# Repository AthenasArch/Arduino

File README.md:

# Arduino - ESP8266 - ESP32 - STM32
- Projetos programados utilizando a interface do Arduino.

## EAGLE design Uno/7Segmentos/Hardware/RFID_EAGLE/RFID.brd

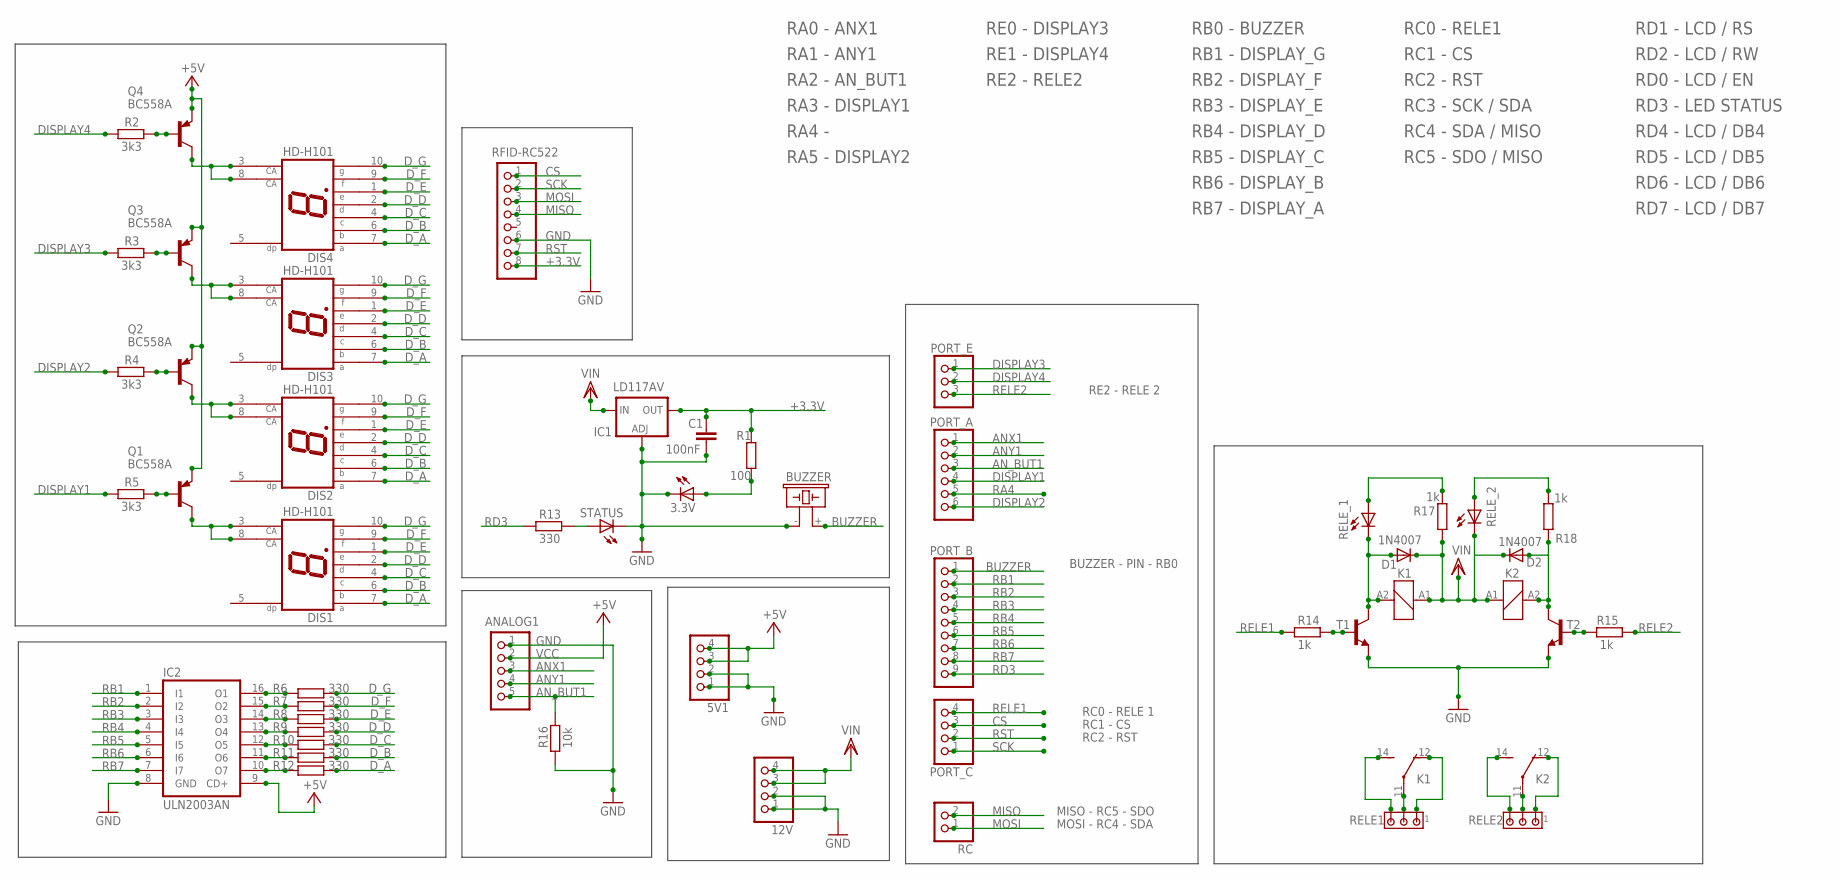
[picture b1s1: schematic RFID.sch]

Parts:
3.3V: LED5MM
5V: BUZZER; F/CM12P
5V1, 12V: PINHD-1X4; 1X04
ANALOG1: PINHD-1X5; 1X05
C1: 100nF; C050-025X075
D1, D2: 1N4007; DO41-10
DIS1, DIS2, DIS3, DIS4: HD-H101; HDSP-M
IC1: LD117AV; TO220L1
IC2: ULN2003AN; DIL16
JP1: RFID-RC522; 1X08
K1, K2: ZNS5106; ZN5
PORT_A: PINHD-1X6; 1X06
PORT_B: PINHD-1X9; 1X09
PORT_C: PINHD-1X4; 1X04
PORT_E: PINHD-1X3; 1X03
Q1, Q2, Q3, Q4: BC558A; TO92-EBC
R1: 100; 0207/10
R2, R3, R4, R5: 3k3; 0207/10
R6, R7, R8, R9, R10, R11, R12, R13: 330; 0207/10
R14, R15, R17, R18: 1k; 0207/10
R16: 10k; 0207/10
RC: PINHD-1X2; 1X02
RELE1, RELE2: MTA03-156; 1X3MTA
RELE_1, RELE_2: LED5MM
STATUS: LED5MM
T1, T2: BC548-NPN-TO92-CBE; TO92-CBE

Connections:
+3.3V: C1.1, IC1.2 (OUT), JP1.8, R1.2
ANX1: ANALOG1.3, PORT_A.1
ANY1: ANALOG1.4, PORT_A.2
AN_BUT1: ANALOG1.5, PORT_A.3, R16.1
BUZZER: 5V.+ (1), PORT_B.1
CS: JP1.1, PORT_C.3
DISPLAY1: PORT_A.4, R5.2
DISPLAY2: PORT_A.6, R4.2
DISPLAY3: PORT_E.1, R3.2
DISPLAY4: PORT_E.2, R2.2
D_A: DIS1.7 (A), DIS2.7 (A), DIS3.7 (A), DIS4.7 (A), R12.1
D_B: DIS1.6 (B), DIS2.6 (B), DIS3.6 (B), DIS4.6 (B), R11.1
D_C: DIS1.4 (C), DIS2.4 (C), DIS3.4 (C), DIS4.4 (C), R10.1
D_D: DIS1.2 (D), DIS2.2 (D), DIS3.2 (D), DIS4.2 (D), R9.1
D_E: DIS1.1 (E), DIS2.1 (E), DIS3.1 (E), DIS4.1 (E), R8.1
D_F: DIS1.9 (F), DIS2.9 (F), DIS3.9 (F), DIS4.9 (F), R7.1
D_G: DIS1.10 (G), DIS2.10 (G), DIS3.10 (G), DIS4.10 (G), R6.1
GND: 3.3V.K (C), 5V.- (2), 5V1.1, 5V1.2, 12V.1, 12V.2, ANALOG1.1, C1.2, IC1.1 (ADJ), IC2.8 (GND), JP1.6, R16.2, STATUS.K (C), T1.E, T2.E
MISO: JP1.4, RC.2
MOSI: JP1.3, RC.1
unnamed: 3.3V.A, R1.1
unnamed: DIS4.3 (CA), DIS4.8 (CA), Q4.C
unnamed: Q1.B, R5.1
unnamed: Q2.B, R4.1
unnamed: Q3.B, R3.1
unnamed: Q4.B, R2.1
unnamed: IC2.16 (O1), R6.2
unnamed: IC2.15 (O2), R7.2
unnamed: IC2.14 (O3), R8.2
unnamed: IC2.13 (O4), R9.2
unnamed: IC2.12 (O5), R10.2
unnamed: IC2.11 (O6), R11.2
unnamed: IC2.10 (O7), R12.2
unnamed: D2.A, K2.A2 (2), R18.2, T2.C
unnamed: R13.1, STATUS.A
unnamed: D1.A, K1.A2 (2), RELE_1.K (C), T1.C
unnamed: R14.1, T1.B
unnamed: K1.11, RELE1.2
unnamed: R15.2, T2.B
unnamed: K1.12 (O), RELE1.1
unnamed: K1.14 (S), RELE1.3
unnamed: K2.11, RELE2.2
unnamed: K2.14 (S), RELE2.3
unnamed: K2.12 (O), RELE2.1
unnamed: R17.2, RELE_1.A
unnamed: R18.1, RELE_2.A
RA4: PORT_A.5
RB1: IC2.1 (I1), PORT_B.2
RB2: IC2.2 (I2), PORT_B.3
RB3: IC2.3 (I3), PORT_B.4
RB4: IC2.4 (I4), PORT_B.5
RB5: IC2.5 (I5), PORT_B.6
RB6: IC2.6 (I6), PORT_B.7
RB7: IC2.7 (I7), PORT_B.8
RD3: PORT_B.9, R13.2
RELE1: PORT_C.4, R14.2
RELE2: PORT_E.3, R15.1
RST: JP1.7, PORT_C.2
SCK: JP1.2, PORT_C.1
VCC: 5V1.3, 5V1.4, ANALOG1.2, IC2.9 (CD+), Q1.E, Q2.E, Q3.E, Q4.E
VCC1: DIS3.3 (CA), DIS3.8 (CA), Q3.C
VCC2: DIS2.3 (CA), DIS2.8 (CA), Q2.C
VCC3: DIS1.3 (CA), DIS1.8 (CA), Q1.C
VDD: 12V.3, 12V.4, D1.C, D2.C, IC1.3 (IN), K1.A1 (1), K2.A1 (1), R17.1, RELE_2.K (C)

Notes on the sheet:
RC2 - RST
RC1 - CS
MOSI - RC4 - SDA
MISO - RC5 - SDO
RE2 - RELE 2
RC0 - RELE 1
BUZZER - PIN - RB0
RA0 - ANX1
RA1 - ANY1
RA2 - AN_BUT1
RA3 - DISPLAY1
RA4 -
RA5 - DISPLAY2
RE2 - RELE2
RE1 - DISPLAY4
RE0 - DISPLAY3
RB0 - BUZZER
RB1 - DISPLAY_G
RB2 - DISPLAY_F
RB3 - DISPLAY_E
RB4 - DISPLAY_D
RB5 - DISPLAY_C
RB6 - DISPLAY_B
RB7 - DISPLAY_A
RC0 - RELE1
RC3 - SCK / SDA
RC4 - SDA / MISO
RC5 - SDO / MISO
RD1 - LCD / RS
RD2 - LCD / RW
RD0 - LCD / EN
RD4 - LCD / DB4
RD5 - LCD / DB5
RD6 - LCD / DB6
RD7 - LCD / DB7
RD3 - LED STATUS

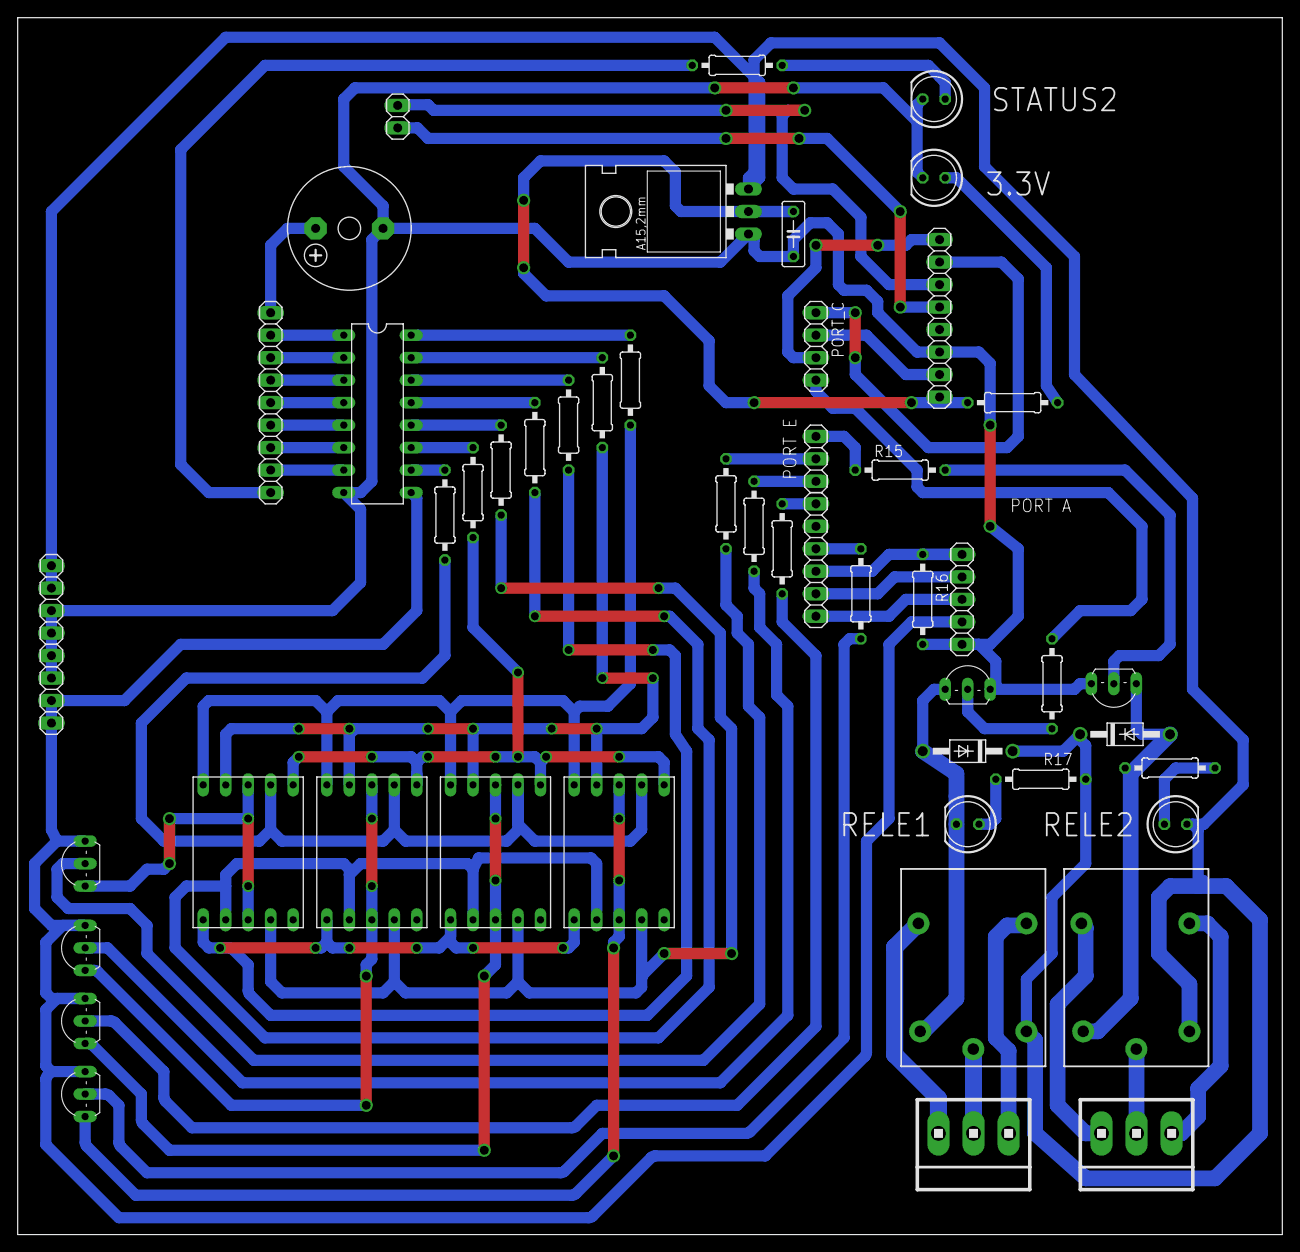
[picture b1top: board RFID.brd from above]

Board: 2 copper layers, 142.9 x 137.5 mm, 51 parts (0 on the bottom side), 63 nets.

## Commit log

2023-06-06 V1.0.1 - Adicionado display de 7 segmentos
    - Adicionado o Hardware muito antigo que desenvolvi para lidar com PIC.
    - E o firmware para o Arduino
